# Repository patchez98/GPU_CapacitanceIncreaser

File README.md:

# Meanwell_EPP_CapacitanceIncreaser

# Purpose
This board is intened to improve stability in PCs that struggle due to high instantaneous current draw in modern GPUs. It adds a bunch of capacitance in a board that screws onto the Meanwell EPP-series PSU's 12V output, in the hopes that it can help the PSU deal with current spikes better. I currently am running a 12V system with a MeanWell EPP-400 that struggles with peak current draw on a 3060ti.

## Form factor
The current version uses a small PCB that is slightly narrower than the EPP and mounts using the screw terminals. It has two XT30 outputs. One is intended for the GPU, one for the plugin DC-DC ATX board and CPU. I only put a single output for the DC-DC and CPU power since some DC-DC boards are intended for passthrough. 

## Capabilities
XT30s are rated for 15A continuous, 30A peak current rating. At 12V, this is 180W continuous, 360W peak. My 3060ti pulls 200W, but I'll keep an eye on it and see how the connector heats up after long use. It has a lot of copper to sink heat into and some nearby airflow, so it should be fine. If I don't make an XT60 version, mine didn't catch on fire.

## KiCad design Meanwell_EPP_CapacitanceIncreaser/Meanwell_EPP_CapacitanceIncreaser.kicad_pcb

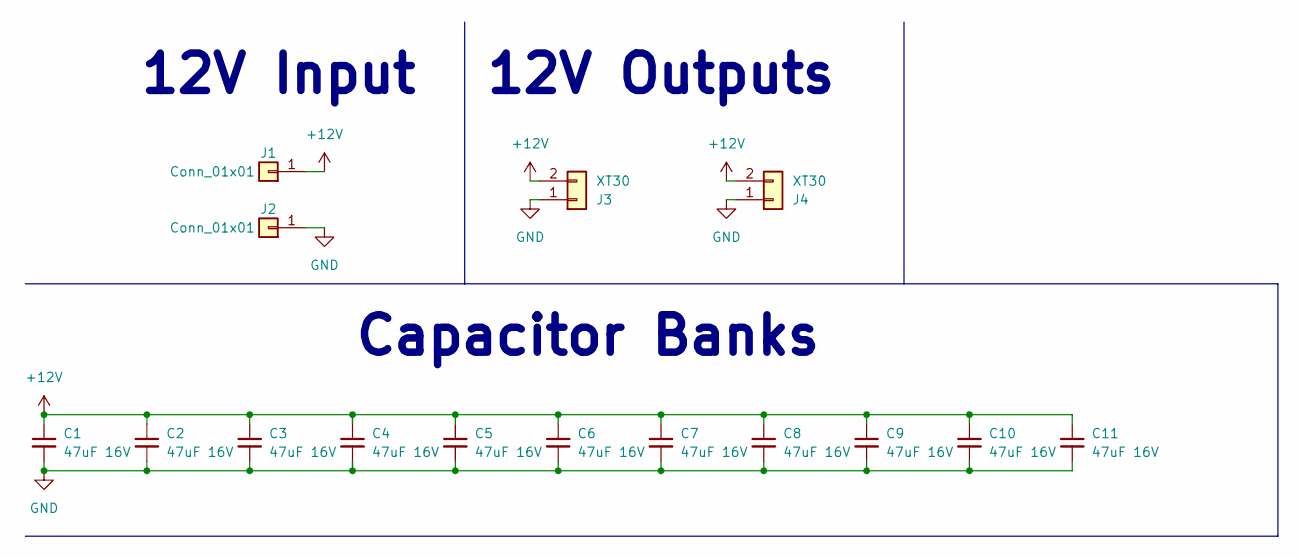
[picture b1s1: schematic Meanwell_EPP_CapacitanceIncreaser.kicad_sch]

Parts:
C1, C2, C3, C4, C5, C6, C7, C8, C9, C10, C11: 47uF 16V; C_1210_3225Metric
J1, J2: Conn_01x01; M3.5
J3, J4: XT30; AMASS_XT30U-F_1x02_P5.0mm_Vertical

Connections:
+12V: C1.1, C2.1, C3.1, C4.1, C5.1, C6.1, C7.1, C8.1, C9.1, C10.1, C11.1, J1.1, J3.2, J4.2
GND: C1.2, C2.2, C3.2, C4.2, C5.2, C6.2, C7.2, C8.2, C9.2, C10.2, C11.2, J2.1, J3.1, J4.1

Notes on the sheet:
12V Outputs
12V Input
Capacitor Banks

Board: 2 copper layers, 15 parts (0 on the bottom side), 2 nets, no tracks yet.

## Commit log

2022-12-10 Added files that I should have added when I made the project
